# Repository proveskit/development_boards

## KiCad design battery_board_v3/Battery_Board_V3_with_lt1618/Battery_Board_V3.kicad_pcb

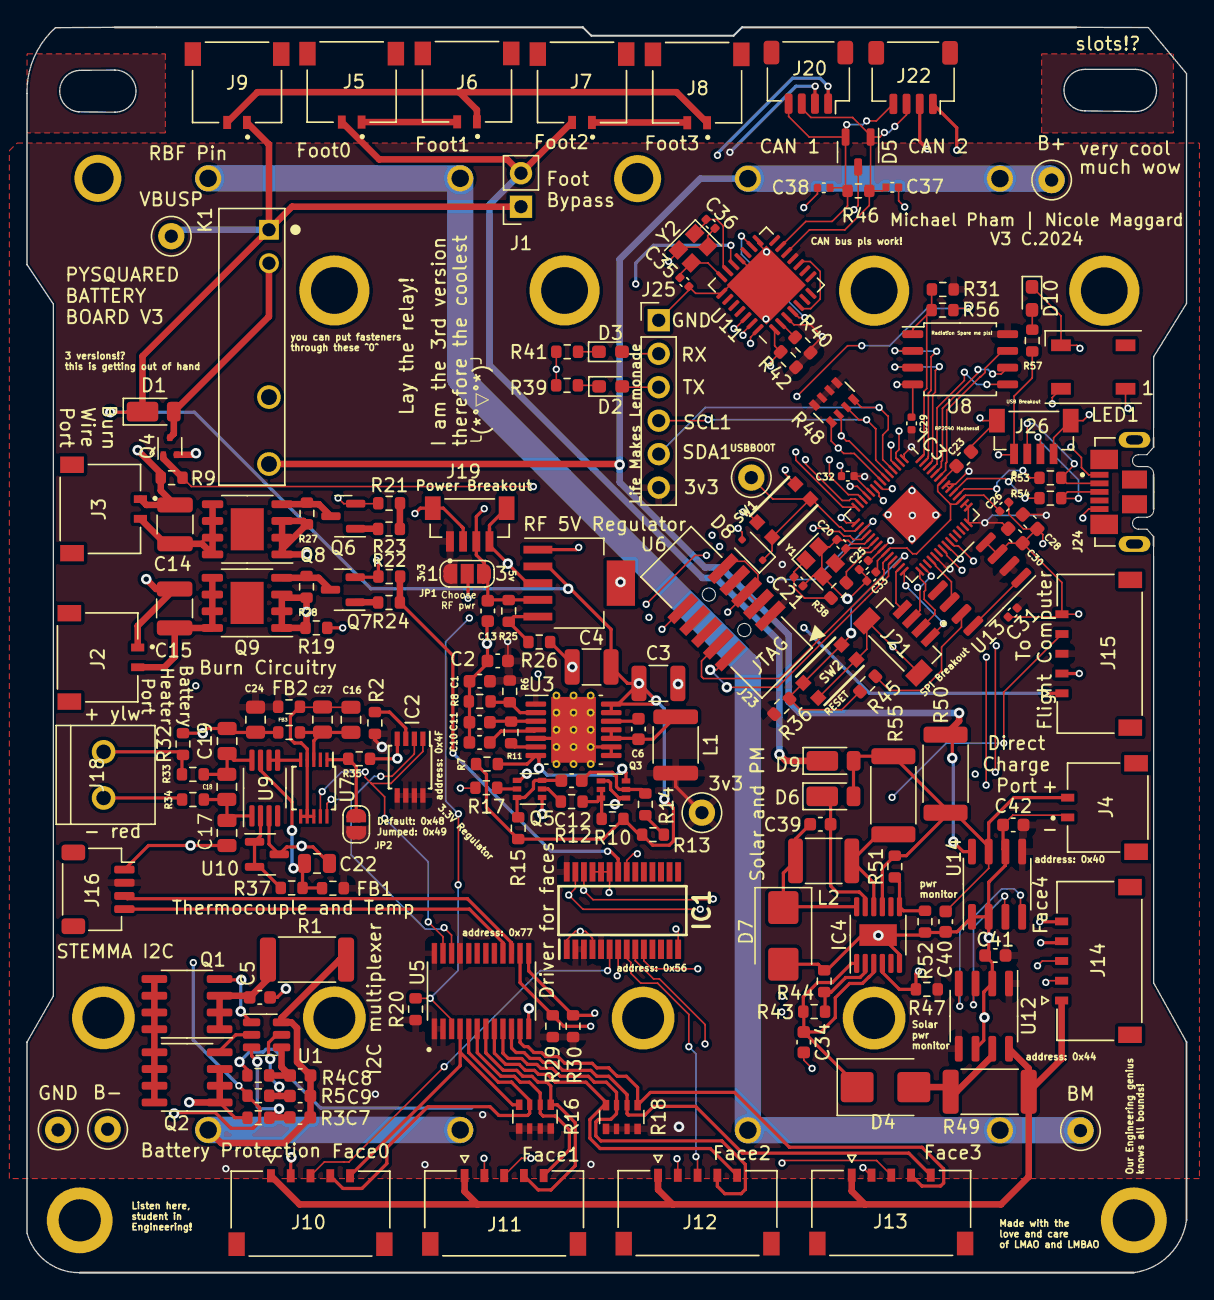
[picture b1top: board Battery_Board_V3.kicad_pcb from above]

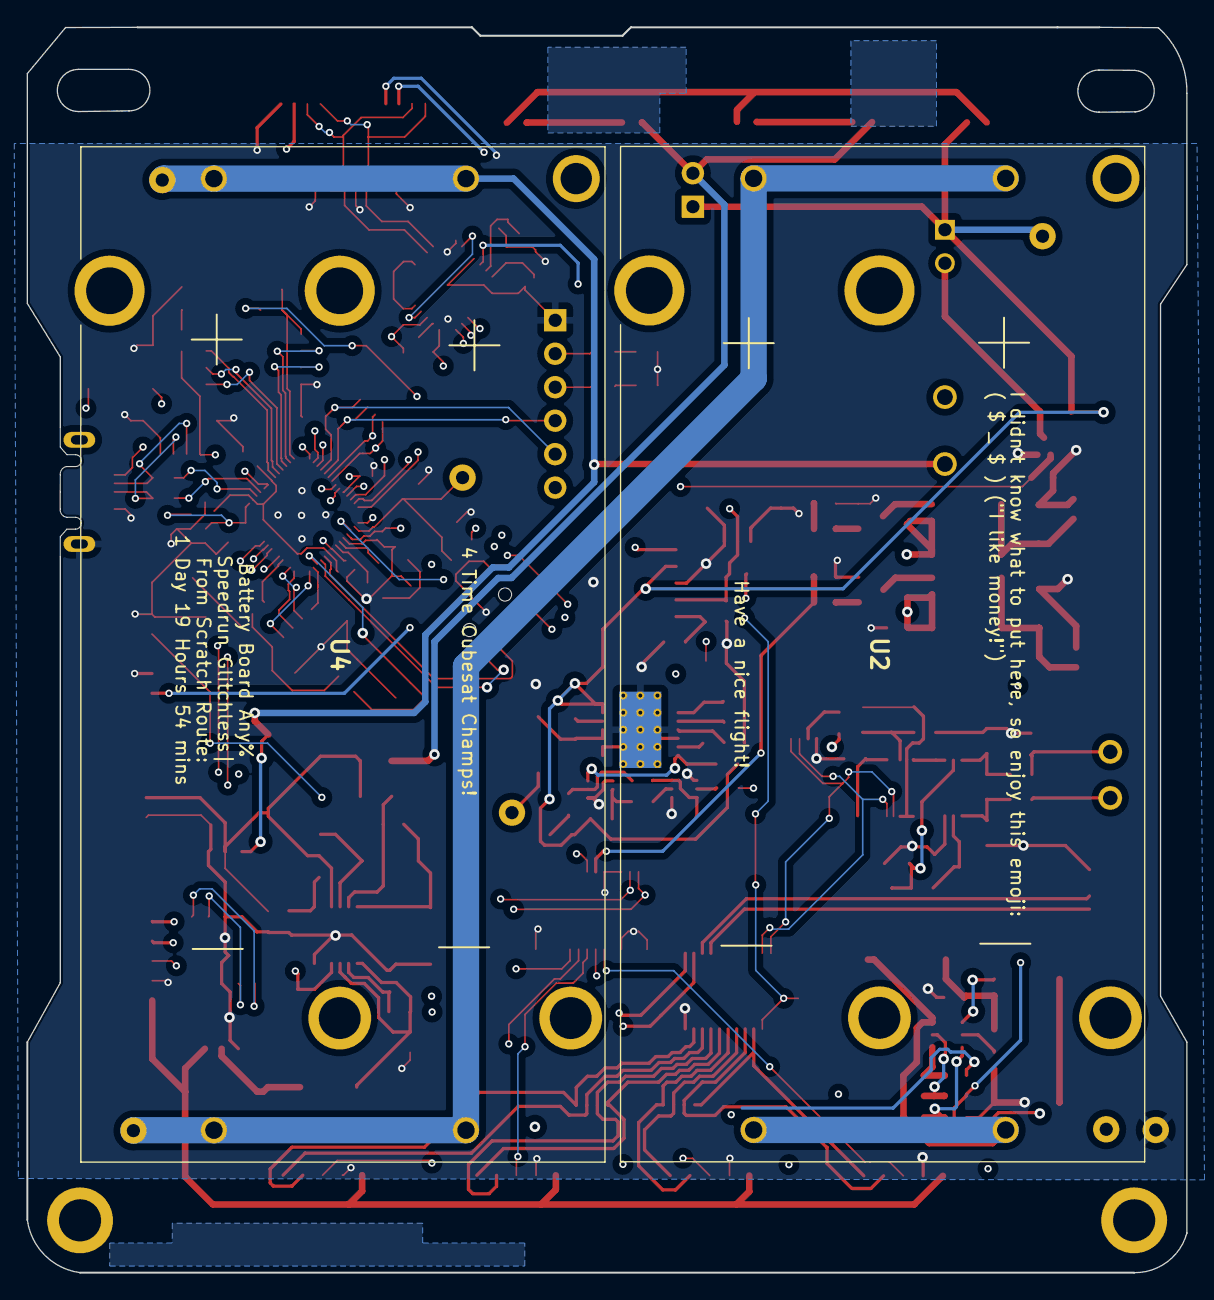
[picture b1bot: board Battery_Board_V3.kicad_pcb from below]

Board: 4 copper layers, 88.0 x 94.5 mm, 181 parts (2 on the bottom side), 135 nets.

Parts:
C1, C2: 22uF; C_0603_1608Metric
C3, C4: 100uF; C_1210_3225Metric
C5, C6, C7, C8, C9, C41, C42: 0.1uF; C_0603_1608Metric
C10: 3.3nF; C_0603_1608Metric
C11, C23, C28, C30, C39: 1uF; C_0603_1608Metric
C12, C13, C34, C40: 10uF; C_0603_1608Metric
C14, C15: 200uF; C_1210_3225Metric
C16, C24: 10uF; C_0805_2012Metric
C17, C19: 0.01uF; C_0805_2012Metric
C18, C27: 0.1uF; C_0805_2012Metric
C20, C21: 22pF; C_0402_1005Metric
C22: 1uF; C_0805_2012Metric
C25, C26, C29, C31, C32, C33: 0.1uF; C_0402_1005Metric
C35, C36: 22pf; C_0402_1005Metric
C37, C38: 47pf; C_0402_1005Metric
D1, D6, D9: DFLS130L; D_PowerDI-123
D2: green; D_0603_1608Metric_Pad1.05x0.95mm_HandSolder
D3: red; D_0603_1608Metric_Pad1.05x0.95mm_HandSolder
D4, D7: D_Schottky; D_SMB
D5: PESD1CAN; SOT-23-3
D8: NSR0320; D_SOD-323F
D10: Blue; D_0603_1608Metric_Pad1.05x0.95mm_HandSolder
FB1, FB2, FB3: FerriteBead; R_0603_1608Metric
IC1: PCA9685PW,118; SOP65P640X110-28N
IC2: PCT2075DP,118; TSSOP-8_3x3mm_P0.65mm
IC3: RP2040_QFN56; QFN-56-1EP_7x7mm_P0.4mm_EP3.2x3.2mm
IC4: LT3652IMSE#PBF; MSOP-12-1EP_3x4mm_P0.65mm_EP1.65x2.85mm
J1: Bypass; PinSocket_1x02_P2.54mm_Vertical
J2: Heater; MOLEX_504050-0291
J3: BURN; MOLEX_504050-0291
J4: CHARGE; MOLEX_504050-0291
J5: Foot0; MOLEX_504050-0291
J6: Foot1; MOLEX_504050-0291
J7: Foot2; MOLEX_504050-0291
J8: Foot3; MOLEX_504050-0291
J9: RBF; MOLEX_504050-0291
J10: Face0; MOLEX_5040500591
J11: Face1; MOLEX_5040500591
J12: Face2; MOLEX_5040500591
J13: Face3; MOLEX_5040500591
J14: Face4; MOLEX_5040500591
J15: FC; MOLEX_5040500591
J16: Breakout; JST_SH_SM04B-SRSS-TB_1x04-1MP_P1.00mm_Horizontal
J18: Screw_Terminal_01x02; ScrewTerminal
J19, J21, J26: BM04B-SRSS-TB(LF)(SN); JST_BM04B-SRSS-TB(LF)(SN)
J20: CAN1; JST_SH_SM04B-SRSS-TB_1x04-1MP_P1.00mm_Horizontal
J22: CAN2; JST_SH_SM04B-SRSS-TB_1x04-1MP_P1.00mm_Horizontal
J23: Conn_ARM_JTAG_SWD_10; JTAG_2X05_1.27MM_BOX_NOCREAM
J24: USB_B_Micro; MOLEX_105164-0001
J25: Life Makes Lemonade; PinHeader_1x06_P2.54mm_Vertical
JP1: SolderJumper_3_Open; SolderJumper-3_P1.3mm_Open_RoundedPad1.0x1.5mm_NumberLabels
JP2: SolderJumper_2_Open; SolderJumper-2_P1.3mm_Open_RoundedPad1.0x1.5mm
K1: APAN3105; RELAY_APAN3105
L1: 3.3uH; L_1812_4532Metric
L2: 10uH; L_1812_4532Metric
LED1: WS2812B_SK6812_1515; LED_WS2812B_PLCC4_5.0x5.0mm_P3.2mm
Q1, Q2: IRF7458; SOIC-8_3.9x4.9mm_P1.27mm
Q3, Q5: MBT2222ADW1T1; SOT-363_SC-70-6
Q4: MMBT2222AT; SOT-523
Q6, Q7: IRLML2803; SOT-23
Q8, Q9: NDS8434; SOIC-8-1EP_3.9x4.9mm_P1.27mm_EP2.514x3.2mm
R1: 0.01; R_2512_6332Metric
R2, R17, R20, R25, R29, R30, R47: 10K; R_0603_1608Metric
R3: 1K; R_0603_1608Metric
R4, R5: 330; R_0603_1608Metric
R6, R7: 73.2K; R_0603_1608Metric
R8: 22.1K; R_0603_1608Metric
R9, R21, R22, R31, R36, R40, R42, R45, R57: 10k; R_0603_1608Metric
R10, R11, R13, R14, R15: 100K; R_0603_1608Metric
R12: 20K; R_0603_1608Metric
R16, R18, R48: 10k; R_Array_Convex_4x0603
R19, R51: 634k; R_0603_1608Metric
R23, R24: 4.7k; R_0603_1608Metric
R26: 3.3K; R_0603_1608Metric
R27, R28: 100k; R_0603_1608Metric
R32: 1-MOhm; R_0603_1608Metric
R33, R34: 100-Ohm; R_0603_1608Metric
R35: 10k-Ohm; R_0603_1608Metric
R37, R38, R39, R41, R56: 1k; R_0603_1608Metric
R43: 200k; R_0603_1608Metric
R44: 85k; R_0603_1608Metric
R46: 120; R_0603_1608Metric
R49, R50: 0.002; R_2512_6332Metric
R52: 412k; R_0603_1608Metric
R53, R54: 22; R_0603_1608Metric
R55: 0.1; R_2512_6332Metric
SW1, SW2: KMR2; BTN_KMR2_4.6X2.8
TP1: 3v3; TestPoint_Loop_D1.80mm_Drill1.0mm_Beaded
TP2: B-; TestPoint_Loop_D1.80mm_Drill1.0mm_Beaded
TP3: BM; TestPoint_Loop_D1.80mm_Drill1.0mm_Beaded
TP4: GND; TestPoint_Loop_D1.80mm_Drill1.0mm_Beaded
TP5: B+; TestPoint_Loop_D1.80mm_Drill1.0mm_Beaded
TP6: VBUSP; TestPoint_Loop_D1.80mm_Drill1.0mm_Beaded
TP8: USBBOOT; TestPoint_Loop_D1.80mm_Drill1.0mm_Beaded
U1: R5460N208AA; SOT-23-6
U2, U4: 1049
U3: TPS54226PWPRPWP14_2P31X2P46-L; HTSSOP-14-1EP_4.4x5mm_P0.65mm_EP3.4x5mm_Mask3x3.1mm_Thermal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
U5: TCA9548APWR; SOP65P640X120-24N
U6: TPS7A4501DCQT; SOT-223-6
U7: ADS1015IDGS; TSSOP-10_3x3mm_P0.5mm
U8: W25Q128JV; SOIC-8_5.275x5.275mm_P1.27mm
U9: AD8495; MSOP-8_3x3mm_P0.65mm
U10: TLVH431 DBZ SOT-23; SOT-23
U11: MCP25625-E/ML; QFN-28-1EP_6x6mm_P0.65mm_EP4.25x4.25mm
U12, U14: INA219AxD; SOIC-8_3.9x4.9mm_P1.27mm
U13: MAX706RESA; SO-8_3.9x4.9mm_P1.27mm
Y1, Y2: Crystal_GND24; Crystal_SMD_2520-4Pin_2.5x2.0mm

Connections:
1.2V: C23.1, C25.2, C26.2, IC3.23 (DVDD), IC3.45 (VREG_VOUT), IC3.50 (DVDD)
+3V3: C1.2, C2.2, C24.2, C28.1, C29.1, C30.1, C31.1, C32.1, C33.1, C41.2, C42.2, FB1.2, FB2.2, IC1.2 (A1), IC1.3 (A2), IC1.5 (A4), IC1.28 (VDD), IC2.5 (A2), IC2.6 (A1), IC2.7 (A0), IC2.8 (VCC), IC3.1 (IOVDD), IC3.10 (IOVDD), IC3.22 (IOVDD), IC3.33 (IOVDD), IC3.42 (IOVDD), IC3.43 (ADC_IOVDD), IC3.44 (VREG_IOVDD), IC3.48 (USB_IOVDD), IC3.49 (IOVDD), J15.3, J16.2, J19.1, J20.2, J22.2, J23.1 (VTref), J25.6, JP1.1 (A), JP2.2 (B), L1.2, R2.1, R6.2, R16.5 (R4.2), R16.6 (R3.2), R16.7 (R2.2), R16.8 (R1.2), R18.5 (R4.2), R18.6 (R3.2), R18.7 (R2.2), R18.8 (R1.2), R20.1, R29.1, R30.1, R31.1, R36.1, R40.1, R42.1, R47.1, R48.5 (R4.2), R48.6 (R3.2), R48.7 (R2.2), R48.8 (R1.2), TP1.1, U3.1 (VO), U5.1 (A0), U5.2 (A1), U5.21 (A2), U5.24 (VCC), U8.8 (VCC), U11.3 (VDD@1), U11.11 (VIO), U12.1 (A1), U12.5 (VS), U13.2 (VCC), U14.5 (VS)
+5V: C13.2, J19.3, JP1.3 (B), R25.1, U6.4 (OUT), U11.19 (VDDA)
/3V3_EN: Q3.6 (C1), R7.2, U3.7 (EN)
/QSPI_CS: IC3.56 (~QSPI_CS), R31.2, R56.1, U8.1 (SSEL)
/QSPI_DATA[0]: IC3.53 (QSPI_SD0), U8.5 (MOSI)
/QSPI_DATA[1]: IC3.55 (QSPI_SD1), U8.2 (MISO)
/QSPI_DATA[2]: IC3.54 (QSPI_SD2), U8.3 (WP#/IO2)
/QSPI_DATA[3]: IC3.51 (QSPI_SD3), U8.7 (HOLD#/IO3)
/QSPI_SCK: IC3.52 (QSPI_SCLK), U8.6 (SCK)
/USBBOOT: D8.C, IC3.16 (GPIO13), SW1.A, SW1.A' (P1), TP8.1
/VDD: C9.2, R5.2, U1.5 (VDD)
/V_RF: J15.1, JP1.2 (C)
/~RESET: IC3.26 (/RUN), J23.10 (~RESET), R36.2, R45.1, SW2.A, SW2.A' (P1)
AGND: C16.2, C27.2, FB3.1, U7.3 (GND)
AVDD: C16.1, C27.1, FB2.1, U7.4 (AIN0), U7.6 (AIN2), U7.7 (AIN3), U7.8 (VDD)
B-: C7.1, C8.1, C9.1, R1.1, TP2.1, U1.6 (VSS), U2.6, U2.7
BM: R4.1, TP3.1, U2.8, U2.9, U4.6, U4.7
BURN: C14.1, J3.2, Q8.5 (Drain), Q8.6 (Drain), Q8.7 (Drain), Q8.8 (Drain)
BURN_RELAY_A: IC3.18 (GPIO15), Q4.1 (B), R9.1
Break_SCL: J16.4, U5.16 (SC5)
Break_SDA: J16.3, U5.15 (SD5)
CANH: C38.2, D5.2, J20.4, J22.4, R46.2, U11.13 (CANH)
CANL: C37.1, D5.1, J20.3, J22.3, R46.1, U11.12 (CANL)
CHRG': IC3.35 (GPIO23), IC4.4 (~CHRG), R47.2
D+: J24.3 (D+), J26.3, R54.2
D-: J24.2 (D-), J26.2, R53.2
ENAB_BURN: R21.1, R23.2
ENAB_HEATER: IC1.22 (LED15), R22.1, R24.2
ENAB_RF: IC3.15 (GPIO12), U6.1 (~SHDN)
F0_ENB: IC1.6 (LED0), J10.3
F0_SCL: J10.4, R16.3 (R3.1), U5.5 (SC0)
F0_SDA: J10.5, R16.4 (R4.1), U5.4 (SD0)
F1_ENB: IC1.7 (LED1), J11.3
F1_SCL: J11.4, R16.1 (R1.1), U5.7 (SC1)
F1_SDA: J11.5, R16.2 (R2.1), U5.6 (SD1)
F2_ENB: IC1.8 (LED2), J12.3
F2_SCL: J12.4, R18.3 (R3.1), U5.9 (SC2)
F2_SDA: J12.5, R18.4 (R4.1), U5.8 (SD2)
F3_ENB: IC1.9 (LED3), J13.3
F3_SCL: J13.4, R18.1 (R1.1), U5.11 (SC3)
F3_SDA: J13.5, R18.2 (R2.1), U5.10 (SD3)
F4_ENB: IC1.10 (LED4), J14.3
F4_SCL: J14.4, R29.2, U5.14 (SC4)
F4_SDA: J14.5, R30.2, U5.13 (SD4)
FC_RESET: IC1.21 (LED14), J15.4
FC_RX: D3.A, IC3.2 (GPIO0), J25.2
FC_TX: D2.A, IC3.3 (GPIO1), J25.3
GND: C1.1, C2.1, C3.2, C4.2, C5.2, C10.2, C11.2, C13.1, C14.2, C15.2, C17.1, C19.2, C20.1, C21.1, C22.2, C23.2, C24.1, C25.1, C26.1, C28.2, C29.2, C30.2, C31.2, C32.2, C33.2, C34.2, C35.2, C36.2, C37.2, C38.1, C40.2, C41.1, C42.1, D5.3, D7.2 (A), D10.C, FB3.2, IC1.1 (A0), IC1.4 (A3), IC1.14 (VSS), IC1.23 (~OE), IC1.24 (A5), IC1.25 (EXTCLK), IC2.4 (GND), IC3.19 (TESTEN), IC3.57 (GND), IC4.6 (TIMER), IC4.13 (EP), J2.1, J3.1, J4.1, J10.2, J11.2, J12.2, J13.2, J14.2, J15.2, J15.5, J16.1, J19.2, J19.4, J19.S1 (SHIELD), J19.S2 (SHIELD), J20.1, J21.S1 (SHIELD), J21.S2 (SHIELD), J22.1, J23.3 (GND), J23.5 (GND), J23.9 (GNDDetect), J24.5 (GND), J24.SH1 (Shield), J25.1, J26.4, J26.S1 (SHIELD), J26.S2 (SHIELD), LED1.3 (GND), Q2.1 (S), Q2.2 (S), Q2.3 (S), Q3.1 (E1), Q3.4 (E2), Q4.2 (E), Q5.1 (E1), Q5.4 (E2), Q6.2 (S), Q7.2 (S), R3.2, R8.1, R9.2, R19.1, R21.2, R22.2, R26.2, R32.2, R35.1, R39.2, R41.2, R44.1, R52.1, SW1.B (S), SW1.B' (S1), SW2.B (S), SW2.B' (S1), TP4.1, U3.5 (GND), U3.8 (PGND1), U3.9 (PGND2), U3.15 (EPAD), U5.12 (GND), U6.3 (GND_1), U6.6 (GND_2), U8.4 (VSS), U9.3 (-Vs), U10.3 (A), U11.15 (STBY), U11.18 (VSS@1), U11.22 (GND), U11.29 (GND@1), U12.2 (A0), U12.6 (GND), U13.3 (GND), U13.4 (PFI), U14.1 (A1), U14.2 (A0), U14.6 (GND), Y1.2, Y1.4, Y2.2, Y2.4
Heater: C15.1, J2.2, Q9.5 (Drain), Q9.6 (Drain), Q9.7 (Drain), Q9.8 (Drain)
I2C_RESET: IC3.9 (GPIO7), R20.2, U5.3 (~RESET)
NEOPIX: IC3.36 (GPIO24), LED1.4 (DI)
NEO_PWR: IC3.37 (GPIO25), LED1.1 (VDD)
unnamed: C5.1, Q1.1 (S), Q1.2 (S), Q1.3 (S), R1.2
unnamed: C21.2, R38.2, Y1.1
unnamed: D2.C, R39.1
unnamed: D3.C, R41.1
unnamed: C34.1, D4.1 (K), IC4.1 (VIN), IC4.3 (~SHDN), R43.1
unnamed: C39.1, D7.1 (K), IC4.12 (SW), L2.1
unnamed: D8.A, R56.2
unnamed: D10.A, R57.2
unnamed: IC2.3 (OS), R2.2
unnamed: C20.2, IC3.20 (XIN), Y1.3
unnamed: IC3.21 (XOUT), R38.1
unnamed: C39.2, D6.C, IC4.11 (BOOST)
unnamed: IC4.10 (SENSE), L2.2, R55.2
unnamed: IC4.7 (VFB), R51.1, R52.2
unnamed: IC4.2 (VIN_REG), R43.2, R44.2
unnamed: J5.1, J6.2
unnamed: J7.1, J8.2
unnamed: J18.1, R33.1
unnamed: J18.2, R32.1, R34.2
unnamed: JP2.1 (A), R35.2, U7.1 (ADDR)
unnamed: K1.NO, Q8.1 (Source), Q8.2 (Source), Q8.3 (Source), Q9.1 (Source), Q9.2 (Source), Q9.3 (Source), R19.2, R27.2, R28.2
unnamed: Q1.5 (D), Q1.6 (D), Q1.7 (D), Q1.8 (D), Q2.5 (D), Q2.6 (D), Q2.7 (D), Q2.8 (D)
unnamed: Q1.4 (G), U1.1 (DOUT)
unnamed: Q2.4 (G), U1.2 (COUT)
unnamed: Q3.2 (B1), Q3.3 (C2), R10.2, R12.2
unnamed: C12.2, Q3.5 (B2), R14.2
unnamed: D1.A, K1.C2, Q4.3 (C)
unnamed: Q5.2 (B1), R12.1
unnamed: C12.1, Q5.3 (C2), Q5.6 (C1), R15.2
unnamed: Q5.5 (B2), R17.1
unnamed: Q6.3 (D), Q8.4 (Gate), R27.1
unnamed: Q6.1 (G), R23.1
unnamed: Q7.3 (D), Q9.4 (Gate), R28.1
unnamed: Q7.1 (G), R24.1
unnamed: R13.2, R14.1
unnamed: C7.2, R3.1, U1.3 (V-)
unnamed: C8.2, R4.2, U1.4 (VC)
unnamed: R11.1, U3.6 (PG)
unnamed: C10.1, U3.4 (SS)
unnamed: C6.1, L1.1, U3.10 (SW1), U3.11 (SW2)
unnamed: C6.2, U3.12 (VBST)
unnamed: R6.1, R8.2, U3.2 (VFB)
unnamed: C11.1, R11.2, U3.3 (VREG5)
unnamed: R25.2, R26.1, U6.5 (SENSE/ADJ)
unnamed: C18.1, C19.1, R34.1, U9.8 (+IN)
unnamed: C22.1, FB1.1, R37.2, U9.7 (+Vs)
unnamed: C17.2, C18.2, R33.2, U9.1 (-IN)
unnamed: R37.1, U9.2 (REF), U10.1 (K), U10.2 (REF)
unnamed: C35.1, U11.21 (OSC1), Y2.3
unnamed: C36.1, U11.20 (OSC2), Y2.1
unnamed: R40.2, U11.2 (RESET)
unnamed: U13.1 (~MR), U13.8 (~WDO)
unnamed: R45.2, U13.7 (~RESET)
OUT: U7.5 (AIN1), U9.5 (SENSE), U9.6
PACK+: K1.M, R5.1, R50.2, TP5.1, U4.8, U4.9, U14.8 (IN+)
RXCAN: U11.5 (RXCAN), U11.10 (RXD)
SCL0: IC1.26 (SCL), IC2.2 (SCL), IC3.7 (GPIO5), R48.1 (R1.1), U5.22 (SCL), U7.10 (SCL), U12.4 (SCL), U14.4 (SCL)
SCL1: IC3.5 (GPIO3), J25.4, R48.3 (R3.1)
SDA0: IC1.27 (SDA), IC2.1 (SDA), IC3.6 (GPIO4), R48.2 (R2.1), U5.23 (SDA), U7.9 (SDA), U12.3 (SDA), U14.3 (SDA)
SDA1: IC3.4 (GPIO2), J25.5, R48.4 (R4.1)
SPI0_CS0: IC3.12 (GPIO9), R42.2, U11.1 (CS)
SPI0_MISO: IC3.11 (GPIO8), U11.28 (SO)
SPI0_MOSI: IC3.14 (GPIO11), U11.27 (SI)
SPI0_SCK: IC3.13 (GPIO10), U11.26 (SCK)
SPI1_CS0: IC3.28 (GPIO17), J21.1
SPI1_MISO: IC3.27 (GPIO16), J21.4
SPI1_MOSI: IC3.30 (GPIO19), J21.3
SPI1_SCK: IC3.29 (GPIO18), J21.2
SWCLK: IC3.24 (SWCLK), J23.4 (SWDCLK/TCK)
SWDIO: IC3.25 (SWDIO), J23.2 (SWDIO/TMS)
TXCAN: U11.4 (TXCAN), U11.16 (TXD)
USB_D+: IC3.47 (USB_D+), R54.1
USB_D-: IC3.46 (USB_D-), R53.1
VBATT_SENSE: C40.1, D6.A, D9.A, IC4.9 (BAT), J4.2, R50.1, R51.2, R55.1, U14.7 (IN-)
VBUS: J24.1 (VBUS), J26.1, R57.1
VBUSP: C3.1, C4.1, D1.C, J1.1, J9.1, K1.C1, R7.1, R10.1, R13.1, R15.1, TP6.1, U3.13 (VIN), U3.14 (VCC), U6.2 (IN)
VBUS_RESET: IC3.17 (GPIO14), R17.2
VBatt: D9.C, J1.2, J5.2, J7.2
VBatt1: J6.1, J8.1, J9.2
VSOLAR: J10.1, J11.1, J12.1, J13.1, J14.1, R49.2, U12.8 (IN+)
VSOLAR_I: D4.2 (A), R49.1, U12.7 (IN-)
WDT_WDI: IC3.32 (GPIO21), U13.6 (~WDI)

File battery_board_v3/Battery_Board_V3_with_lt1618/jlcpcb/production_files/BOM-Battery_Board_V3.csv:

Comment,Designator,Footprint,LCSC
FerriteBead,"FB1,FB2,FB3",R_0603_1608Metric,C1002
73.2K,"R6,R7",R_0603_1608Metric,C101180
IRF7458,"Q1,Q2",SOIC-8_3.9x4.9mm_P1.27mm,C10879
0.002,"R49,R50",R_2512_6332Metric,C108929
10k,"R16,R18,R48",R_Array_Convex_4x0603,C111802
TCA9548APWR,U5,SOP65P640X120-24N,C130026
TPS54226PWPRPWP14_2P31X2P46-L,U3,HTSSOP-14-1EP_4.4x5mm_P0.65mm_EP3.4x5mm_Mask3x3.1mm_ThermalVias,C1355858
INA219AxD,"U12,U14",SOIC-8_3.9x4.9mm_P1.27mm,C138706
0.1uF,"C41,C42,C5,C6,C7,C8,C9",C_0603_1608Metric,C14663
DFLS130L,"D1,D6,D9",D_PowerDI-123,C150474
0.1uF,"C25,C26,C29,C31,C32,C33",C_0402_1005Metric,C1525
22pF,"C20,C21,C35,C36",C_0402_1005Metric,C1555
47pf,"C37,C38",C_0402_1005Metric,C1567
PESD1CAN,D5,SOT-23-3,C15771
1uF,"C11,C23,C28,C30,C39",C_0603_1608Metric,C15849
10uF,"C16,C24",C_0805_2012Metric,C15850
BM04B-SRSS-TB(LF)(SN),"J19,J21,J26",JST_BM04B-SRSS-TB(LF)(SN),C160390
Breakout,"J16,J20,J22",JST_SH_SM04B-SRSS-TB_1x04-1MP_P1.00mm_Horizontal,C160404
3.3nF,C10,C_0603_1608Metric,C1613
0.01uF,"C17,C19",C_0805_2012Metric,C1710
MMBT2222AT,Q4,SOT-523,C190608
"PCT2075DP,118",IC2,TSSOP-8_3x3mm_P0.65mm,C192518
ADS1015IDGS,U7,TSSOP-10_3x3mm_P0.5mm,C193969
10uF,"C12,C13,C34,C40",C_0603_1608Metric,C19702
RP2040_QFN56,IC3,QFN-56-1EP_7x7mm_P0.4mm_EP3.2x3.2mm,C2040
1K,"R3,R37,R38,R39,R41,R56",R_0603_1608Metric,C21190
TLVH431 DBZ SOT-23,U10,SOT-23,C2156576
85k,R44,R_0603_1608Metric,C227531
100-Ohm,"R33,R34",R_0603_1608Metric,C22775
120,R46,R_0603_1608Metric,C22787
red,D3,D_0603_1608Metric_Pad1.05x0.95mm_HandSolder,C2286
1-MOhm,R32,R_0603_1608Metric,C22935
3.3K,R26,R_0603_1608Metric,C22978
412k,R52,R_0603_1608Metric,C23050
330,"R4,R5",R_0603_1608Metric,C23138
4.7k,"R23,R24",R_0603_1608Metric,C23162
22,"R53,R54",R_0603_1608Metric,C23345
USB_B_Micro,J24,MOLEX_105164-0001,C234179
200uF,"C14,C15,C3,C4",C_1210_3225Metric,C23742
Crystal_GND24,Y1,Crystal_SMD_2520-4Pin_2.5x2.0mm,C252259
0.1,R55,R_2512_6332Metric,C25466
10K,"R17,R2,R20,R21,R22,R25,R29,R30,R31,R35,R36,R40,R42,R45,R47,R57,R9",R_0603_1608Metric,C25804
200k,R43,R_0603_1608Metric,C25811
22.1K,R8,R_0603_1608Metric,C25961
R5460N208AA,U1,SOT-23-6,C259714
"PCA9685PW,118",IC1,SOP65P640X110-28N,C2678753
0.1uF,"C18,C27",C_0805_2012Metric,C28233
1uF,C22,C_0805_2012Metric,C28323
MAX706RESA,U13,SO-8_3.9x4.9mm_P1.27mm,C28380
Crystal_GND24,Y2,Crystal_SMD_2520-4Pin_2.5x2.0mm,C284158
WS2812B_SK6812_1515,LED1,LED_WS2812B_PLCC4_5.0x5.0mm_P3.2mm,C2843785
D_Schottky,"D4,D7",D_SMB,C2892544
NDS8434,"Q8,Q9",SOIC-8-1EP_3.9x4.9mm_P1.27mm_EP2.514x3.2mm,C2997
Screw_Terminal_01x02,J18,ScrewTerminal,C2997509
20K,R12,R_0603_1608Metric,C4184
100K,"R10,R11,R13,R14,R15,R27,R28",R_0603_1608Metric,C427284
LT3652IMSE#PBF,IC4,MSOP-12-1EP_3x4mm_P0.65mm_EP1.65x2.85mm,C459874
MCP25625-E/ML,U11,QFN-28-1EP_6x6mm_P0.65mm_EP4.25x4.25mm,C481365
NSR0320,D8,D_SOD-323F,C48192
IRLML2803,"Q6,Q7",SOT-23,C558175
MBT2222ADW1T1,"Q3,Q5",SOT-363_SC-70-6,C559075
22uF,"C1,C2",C_0603_1608Metric,C59461
AD8495,U9,MSOP-8_3x3mm_P0.65mm,C59658
634k,"R19,R51",R_0603_1608Metric,C65831
green,D2,D_0603_1608Metric_Pad1.05x0.95mm_HandSolder,C72040
Blue,D10,D_0603_1608Metric_Pad1.05x0.95mm_HandSolder,C72041
KMR2,"SW1,SW2",BTN_KMR2_4.6X2.8,C72443
0.01,R1,R_2512_6332Metric,C76243
TPS7A4501DCQT,U6,SOT-223-6,C840094
W25Q128JV,U8,SOIC-8_5.275x5.275mm_P1.27mm,C97521
10uH,L2,L_1812_4532Metric,C99792
3.3uH,L1,L_1812_4532Metric,C99794
Foot1,J6,MOLEX_504050-0291,
Face1,J11,MOLEX_5040500591,
CHARGE,J4,MOLEX_504050-0291,
FC,J15,MOLEX_5040500591,
Face3,J13,MOLEX_5040500591,
Face2,J12,MOLEX_5040500591,
1049,U2,1049,
1049,U4,1049,
Bypass,J1,PinSocket_1x02_P2.54mm_Vertical,
SolderJumper_3_Open,JP1,SolderJumper-3_P1.3mm_Open_RoundedPad1.0x1.5mm_NumberLabels,
Heater,J2,MOLEX_504050-0291,
APAN3105,K1,RELAY_APAN3105,
BURN,J3,MOLEX_504050-0291,
Foot0,J5,MOLEX_504050-0291,
Face4,J14,MOLEX_5040500591,
VBUSP,TP6,TestPoint_Loop_D1.80mm_Drill1.0mm_Beaded,
B+,TP5,TestPoint_Loop_D1.80mm_Drill1.0mm_Beaded,
GND,TP4,TestPoint_Loop_D1.80mm_Drill1.0mm_Beaded,
BM,TP3,TestPoint_Loop_D1.80mm_Drill1.0mm_Beaded,
B-,TP2,TestPoint_Loop_D1.80mm_Drill1.0mm_Beaded,
3v3,TP1,TestPoint_Loop_D1.80mm_Drill1.0mm_Beaded,
Foot2,J7,MOLEX_504050-0291,
Foot3,J8,MOLEX_504050-0291,
Life Makes Lemonade,J25,PinHeader_1x06_P2.54mm_Vertical,
USBBOOT,TP8,TestPoint_Loop_D1.80mm_Drill1.0mm_Beaded,
Face0,J10,MOLEX_5040500591,
Conn_ARM_JTAG_SWD_10,J23,JTAG_2X05_1.27MM_BOX_NOCREAM,
RBF,J9,MOLEX_504050-0291,
SolderJumper_2_Open,JP2,SolderJumper-2_P1.3mm_Open_RoundedPad1.0x1.5mm,

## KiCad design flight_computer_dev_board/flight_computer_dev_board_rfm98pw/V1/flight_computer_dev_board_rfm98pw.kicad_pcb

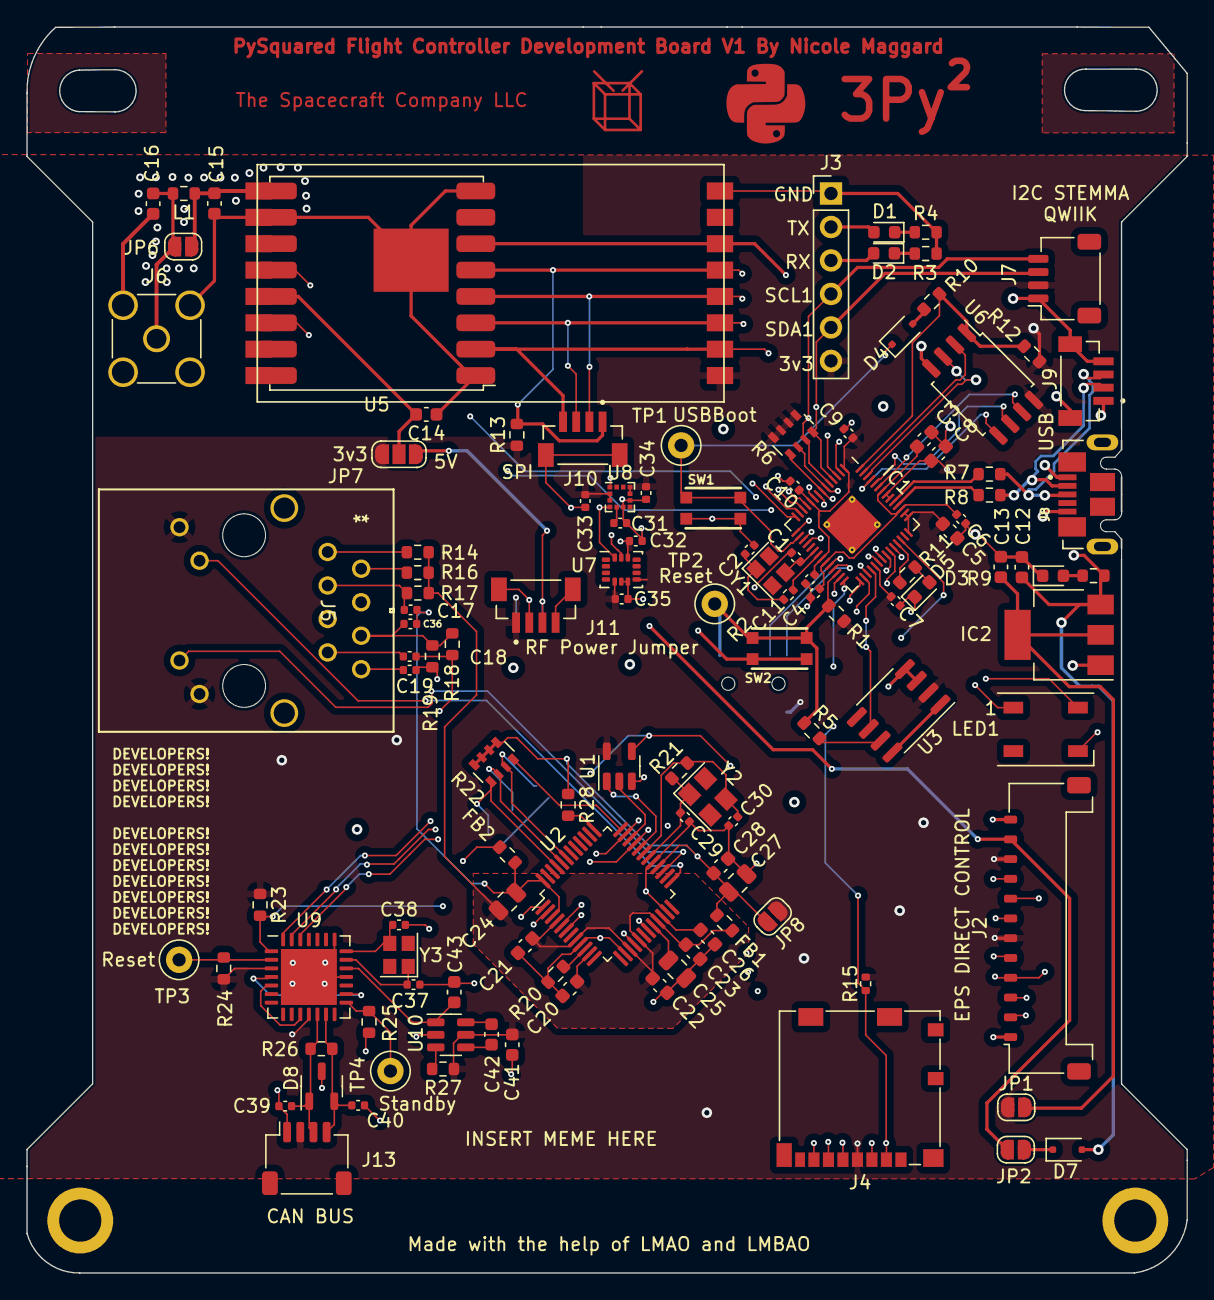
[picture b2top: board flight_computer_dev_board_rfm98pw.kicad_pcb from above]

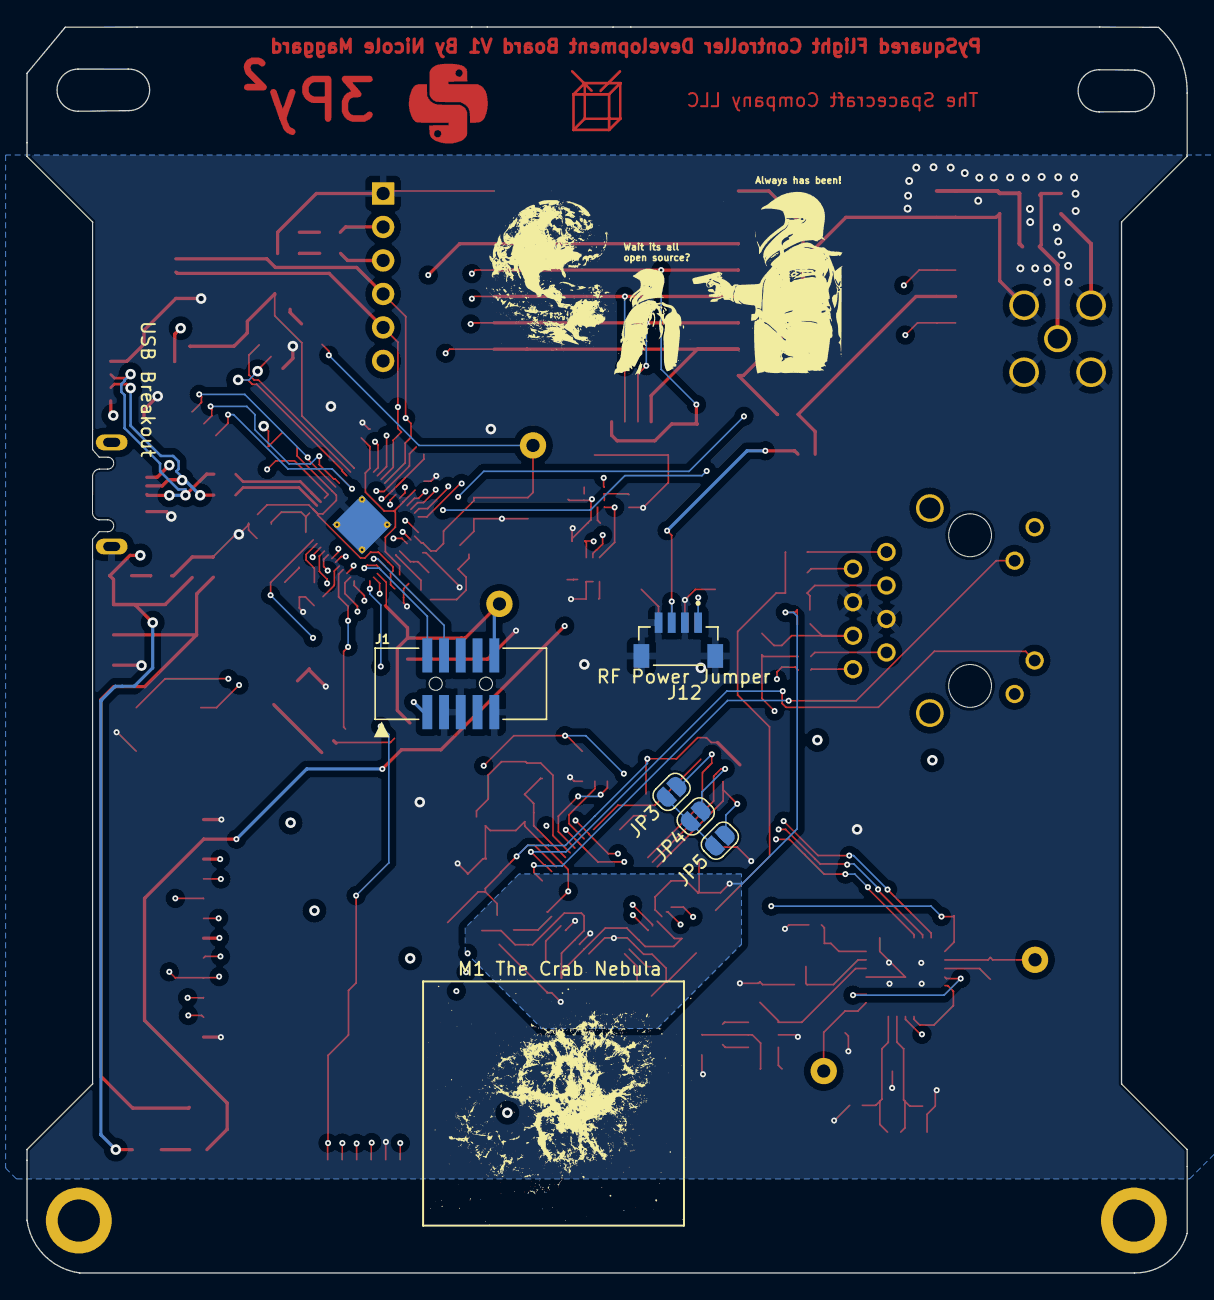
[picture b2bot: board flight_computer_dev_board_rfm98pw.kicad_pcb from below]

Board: 4 copper layers, 88.0 x 94.5 mm, 124 parts (5 on the bottom side), 100 nets.

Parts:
C1, C2, C29, C30: 22pF; C_0402_1005Metric
C3, C6, C8: 1uF; C_0603_1608Metric
C4, C5, C7, C9, C10, C11, C32, C33, C34, C35: 100nf; C_0402_1005Metric
C12, C14: 10uF; C_0603_1608Metric
C13: 22uF; C_0603_1608Metric
C15, C16: DNI; C_0603_1608Metric
C17, C36: 10nf; C_0402_1005Metric
C18, C19: 6.8nf; C_0402_1005Metric
C20, C21, C22, C23, C26, C28: 0.1uF; C_0603_1608Metric
C24, C25, C27: 10uF; C_0805_2012Metric
C31: 220nf; C_0402_1005Metric
C37, C38: 22pf; C_0402_1005Metric
C39, C40: 47pf; C_0402_1005Metric
C41, C43: 10uf; C_0603_1608Metric
C42: 1uf; C_0603_1608Metric
D1, D2, D3, D5: LED; LED_0603_1608Metric
D4, D7: NSR0320; D_SOD-323F
D8: PESD1CAN; SOT-23-3
FB1, FB2: FerriteBead; R_0603_1608Metric
IC1: RP2040_QFN56; QFN-56-1EP_7x7mm_P0.4mm_EP3.2x3.2mm_ThermalVias
IC2: AZ1117CH-3.3TRG1; SOT-223
J1: Conn_ARM_JTAG_SWD_10; JTAG_2X05_1.27MM_BOX_NOCREAM
J2: FC to EPS Connector; Molex_Pico-Lock_504050-1291_1x12-1MP_P1.50mm_Horizontal
J3: Life Makes Lemonade; PinHeader_1x06_P2.54mm_Vertical
J4: 104031-0811; microSD_HC_Molex_104031-0811
J5: RJ45_LED_Shielded; RB1-125BAG1A_WIZ
J6: Conn_Coaxial; SMA_Amphenol_901-144_Vertical
J7, J13: Breakout; JST_SH_SM04B-SRSS-TB_1x04-1MP_P1.00mm_Horizontal
J8: USB_B_Micro; MOLEX_105164-0001
J9, J10, J11, J12: BM04B-SRSS-TB(LF)(SN); JST_BM04B-SRSS-TB(LF)(SN)
JP1, JP2, JP3, JP4, JP5, JP6, JP8: SolderJumper_2_Open; SolderJumper-2_P1.3mm_Open_RoundedPad1.0x1.5mm
JP7: SolderJumper_3_Open; SolderJumper-3_P1.3mm_Open_RoundedPad1.0x1.5mm_NumberLabels
L1: DNI; R_0603_1608Metric
LED1: WS2812B_SK6812_1515; LED_WS2812B_PLCC4_5.0x5.0mm_P3.2mm
R1, R5, R9, R11, R12, R13, R23, R24, R25, R27, R28: 10k; R_0603_1608Metric
R2: 1k; R_0402_1005Metric
R3, R4, R10: 1k; R_0603_1608Metric
R6, R22: 10k; R_Array_Convex_4x0603
R7, R8: 22; R_0603_1608Metric
R14, R16, R18, R19: 49.9; R_0603_1608Metric
R15: 10k; R_0402_1005Metric
R17: 10; R_0603_1608Metric
R20: 12.4k; R_0603_1608Metric
R21: 1M; R_0603_1608Metric
R26: 120; R_0603_1608Metric
SW1, SW2: KMR2; BTN_KMR2_4.6X2.8
TP1: USBBOOT; TestPoint_Loop_D1.80mm_Drill1.0mm_Beaded
TP2, TP3: RESET; TestPoint_Loop_D1.80mm_Drill1.0mm_Beaded
TP4: Standby; TestPoint_Loop_D1.80mm_Drill1.0mm_Beaded
U1: SN74AHC1G125DBVR; SOT-23-5
U2: W5500; LQFP-48_7x7mm_P0.5mm
U3: MAX706RESA; SO-8_3.9x4.9mm_P1.27mm
U4: RFM98PW
U5: RFM9xBreakout; HOPERF_RFM9XW_SMD
U6: W25Q128JV; SOIC-8_5.275x5.275mm_P1.27mm
U7: LSM6DSOTR; LGA-14_3x2.5mm_P0.5mm_LayoutBorder3x4y
U8: LSM303AGRTR; LGA-12_2x2mm_P0.5mm
U9: MCP25625-E/ML; QFN-28-1EP_6x6mm_P0.65mm_EP4.25x4.25mm
U10: AP3602AKTR-G1; SOT-23-6
Y1: 12MHZ; Crystal_SMD_2520-4Pin_2.5x2.0mm
Y2: 25MHz; Crystal_SMD_3225-4Pin_3.2x2.5mm
Y3: 16MHZ 12 pf; Crystal_SMD_2520-4Pin_2.5x2.0mm

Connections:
1.2V: C3.1, C4.2, C5.2, IC1.23 (DVDD), IC1.45 (VREG_VOUT), IC1.50 (DVDD)
3.3V: C6.1, C7.1, C8.1, C9.1, C10.1, C11.1, C32.1, C33.1, C34.1, C35.1, C41.2, IC1.1 (IOVDD), IC1.10 (IOVDD), IC1.22 (IOVDD), IC1.33 (IOVDD), IC1.42 (IOVDD), IC1.43 (ADC_IOVDD), IC1.44 (VREG_IOVDD), IC1.48 (USB_IOVDD), IC1.49 (IOVDD), J1.1 (VTref), J2.6, J2.10, J3.6, J4.4 (VDD), J5.10, J5.12, J7.2, J11.1, J12.1, J13.2, JP1.1 (A), JP7.3 (B), JP8.1 (A), R1.1, R6.5 (R4.2), R6.6 (R3.2), R6.7 (R2.2), R6.8 (R1.2), R12.1, R13.1, R15.2, R23.1, R24.1, R27.1, U1.5 (VCC), U3.2 (VCC), U4.9 (3.3V), U6.8 (VCC), U7.5 (VDDIO), U7.8 (VDD), U7.12 (CS), U8.2 (CS_XL), U8.3 (CS_MAG), U8.9 (VDD), U8.10 (VDD_IO), U9.3 (VDD@1), U9.11 (VIO), U10.5 (VIN)
3v3 Spec: C13.1, IC2.2 (OUTPUT), IC2.4 (VOUT), JP1.2 (B)
3v3_prime: C27.1, C28.1, FB1.1, JP8.2 (B), R22.5 (R4.2), R22.6 (R3.2), R22.7 (R2.2), R22.8 (R1.2), R28.1, U2.28 (VDD)
+5V: C43.2, U9.19 (VDDA), U10.1 (VOUT)
/D+: IC1.47 (USB_D+), R7.1
/D-: IC1.46 (USB_D-), R8.1
/QSPI_CS: IC1.56 (~QSPI_CS), R10.1, R12.2, U6.1 (SSEL)
/QSPI_DATA[0]: IC1.53 (QSPI_SD0), U6.5 (MOSI)
/QSPI_DATA[1]: IC1.55 (QSPI_SD1), U6.2 (MISO)
/QSPI_DATA[2]: IC1.54 (QSPI_SD2), U6.3 (WP#/IO2)
/QSPI_DATA[3]: IC1.51 (QSPI_SD3), U6.7 (HOLD#/IO3)
/QSPI_SCK: IC1.52 (QSPI_SCLK), U6.6 (SCK)
/USBBOOT: D4.1 (K), IC1.16 (GPIO13), SW1.A, SW1.A' (P1), TP1.1
/~RESET: IC1.26 (/RUN), J1.10 (~RESET), R1.2, R5.1, SW2.A, SW2.A' (P1), TP2.1
BURN_RELAY_A: IC1.18 (GPIO15), J2.2
CANH: C40.2, D8.2, J13.4, R26.2, U9.13 (CANH)
CANL: C39.1, D8.1, J13.3, R26.1, U9.12 (CANL)
ENABLE_BURN: IC1.8 (GPIO6), J2.9
ENAB_RF: IC1.15 (GPIO12), J2.5
GND: C1.1, C2.1, C3.2, C4.1, C5.1, C6.2, C7.2, C8.2, C9.2, C10.2, C11.2, C12.2, C13.2, C14.1, C15.2, C16.2, C27.2, C28.2, C29.2, C30.2, C31.2, C32.2, C33.2, C34.2, C35.2, C37.2, C38.2, C39.2, C40.1, C41.1, C43.1, D3.1 (K), D5.1 (K), D8.3, FB2.1, IC1.57 (GND), IC2.1 (ADJ/GND), J1.3 (GND), J1.5 (GND), J1.9 (GNDDetect), J2.1, J2.12, J3.1, J4.6 (VSS), J5.4, J5.5, J6.2 (Ext), J7.1, J8.5 (GND), J8.SH1 (Shield), J9.4, J9.S1 (SHIELD), J9.S2 (SHIELD), J10.S1 (SHIELD), J10.S2 (SHIELD), J11.2, J11.4, J11.S1 (SHIELD), J11.S2 (SHIELD), J12.2, J12.4, J12.S1 (SHIELD), J12.S2 (SHIELD), J13.1, LED1.3 (GND), R3.2, R4.2, R25.1, SW1.B (S), SW1.B' (S1), SW2.B (S), SW2.B' (S1), U1.3 (GND), U2.23 (RSVD), U2.29 (GND), U3.3 (GND), U3.4 (PFI), U4.2 (GND), U4.16 (GND), U4.17 (GND), U5.1 (GND), U5.8 (GND), U5.10 (GND), U6.4 (VSS), U7.6 (GND), U7.7 (GND), U8.6 (GND), U8.8 (GND), U9.18 (VSS@1), U9.22 (GND), U9.29 (GND@1), U10.2 (GND)
GNDA: C17.2, C20.2, C21.2, C22.2, C23.2, C24.2, C25.1, C26.1, C36.2, FB2.2, R20.1, U2.3 (AGND), U2.9 (AGND), U2.14 (AGND), U2.16 (AGND), U2.19 (AGND), U2.48 (AGND)
GREENLED: J5.11, U2.25 (LINKLED)
I2C_RESET: IC1.9 (GPIO7), J2.4
MISO_ETHER: U1.2 (A), U2.34 (MISO)
NEOPIX: IC1.36 (GPIO24), LED1.4 (DI)
NEO_PWR: IC1.37 (GPIO25), LED1.1 (VDD)
unnamed: C2.2, R2.2, Y1.1
unnamed: C18.1, J5.7
unnamed: C19.1, J5.8
unnamed: D1.1 (K), R4.1
unnamed: D2.1 (K), R3.1
unnamed: D3.2 (A), R9.2
unnamed: D4.2 (A), R10.2
unnamed: D5.2 (A), R11.2
unnamed: D7.1 (K), JP2.2 (B)
unnamed: C1.2, IC1.20 (XIN), Y1.3 (2)
unnamed: IC1.21 (XOUT), R2.1
unnamed: C16.1, J6.1 (In), JP6.1 (A), L1.2
unnamed: JP3.1 (A), JP4.1 (A), JP5.1 (A)
unnamed: JP3.2 (B), R22.3 (R3.1), U2.43 (PMODE2)
unnamed: JP4.2 (B), R22.2 (R2.1), U2.44 (PMODE1)
unnamed: JP5.2 (B), R22.1 (R1.1), U2.45 (PMODE0)
unnamed: R22.4 (R4.1), U2.36 (INTN)
unnamed: C26.2, U2.22 (1V20)
unnamed: R20.2, U2.10 (EXRES1)
unnamed: R28.2, U2.37 (RSTN)
unnamed: C25.2, U2.20 (TOCAP)
unnamed: C29.1, R21.1, U2.30 (XI/CLKIN), Y2.1
unnamed: C30.1, R21.2, U2.31 (XO), Y2.3 (2)
unnamed: U3.1 (~MR), U3.8 (~WDO)
unnamed: R5.2, U3.7 (~RESET)
unnamed: C31.1, U8.5 (C1)
unnamed: C38.1, U9.21 (OSC1), Y3.3 (2)
unnamed: C37.1, U9.20 (OSC2), Y3.1
unnamed: R24.2, TP3.1, U9.2 (RESET)
unnamed: R25.2, TP4.1, U9.15 (STBY)
unnamed: R27.2, U10.3 (*SHDN)
unnamed: C42.2, U10.6 (C+)
unnamed: C42.1, U10.4 (C-)
RCT: C36.1, J5.6, R18.2, R19.2
RF1_ANT: C15.1, JP6.2 (B), L1.1, U4.1 (ANT), U5.9 (ANT)
RF1_IO0: IC1.35 (GPIO23), U4.6 (GPIO_0), U5.14 (DIO0)
RF1_IO4: IC1.34 (GPIO22), U4.4 (GPIO_4), U5.12 (BUSY)
RF1_RST: IC1.31 (GPIO20), U4.14 (RESET), U5.6 (~RESET)
RF_VCC: C14.2, JP7.2 (C), U4.5 (VCC), U5.13 (3V3)
RX: D2.2 (A), IC1.3 (GPIO1), J3.3
RX+: C18.2, R18.1, U2.6 (RXP)
RX-: C19.2, R19.1, U2.5 (RXN)
RXCAN: U9.5 (RXCAN), U9.10 (RXD)
SCL0: IC1.7 (GPIO5), J2.7, R6.1 (R1.1)
SCL1: IC1.5 (GPIO3), J3.4, J7.4, R6.3 (R3.1), U7.13 (SCL), U8.1 (SCL/SPC)
SDA0: IC1.6 (GPIO4), J2.8, R6.2 (R2.1)
SDA1: IC1.4 (GPIO2), J3.5, J7.3, R6.4 (R4.1), U7.14 (SDA), U8.4 (SDA/SDI/SDO)
SPI0_CS0: IC1.12 (GPIO9), J10.1, R13.2, U4.13 (NSS), U5.5 (CS)
SPI0_MISO: IC1.11 (GPIO8), J10.4, U4.10 (MISO), U5.2 (MISO)
SPI0_MOSI: IC1.14 (GPIO11), J10.3, U4.11 (MOSI), U5.3 (MOSI)
SPI0_SCK: IC1.13 (GPIO10), J10.2, U4.12 (SCK), U5.4 (SCK)
SPI1_CS0: IC1.28 (GPIO17), J4.2 (CD/DAT3), R15.1
SPI1_CS1: IC1.38 (GPIO26/AD0), U1.1 (*OE), U2.32 (SCSN)
SPI1_CS2: IC1.40 (GPIO28/AD2), R23.2, U9.1 (CS)
SPI1_MISO: IC1.27 (GPIO16), J4.7 (DAT0), U1.4 (Y), U9.28 (SO)
SPI1_MOSI: IC1.30 (GPIO19), J4.3 (CMD), U2.35 (MOSI), U9.27 (SI)
SPI1_SCK: IC1.29 (GPIO18), J4.5 (CLK), U2.33 (SCLK), U9.26 (SCK)
SWCLK: IC1.24 (SWCLK), J1.4 (SWDCLK/TCK)
SWDIO: IC1.25 (SWDIO), J1.2 (SWDIO/TMS)
TCT: C17.1, J5.3, R17.2
TX: D1.2 (A), IC1.2 (GPIO0), J3.2
TX+: J5.1, R14.2, U2.2 (TXP)
TX-: J5.2, R16.2, U2.1 (TXN)
TXCAN: U9.4 (TXCAN), U9.16 (TXD)
USB_D+: J8.3 (D+), J9.3, R7.2
USB_D-: J8.2 (D-), J9.2, R8.2
VBUS: C12.1, D7.2 (A), IC2.3 (INPUT), J8.1 (VBUS), J9.1, R9.1
VBUS_RESET: IC1.17 (GPIO14), J2.3
VCC_RF1: J2.11, J11.3, J12.3, JP2.1 (A), JP7.1 (A)
VDDA: C20.1, C21.1, C22.1, C23.1, C24.1, FB1.2, R14.1, R16.1, R17.1, U2.4 (AVDD), U2.8 (AVDD), U2.11 (AVDD), U2.15 (AVDD), U2.17 (AVDD), U2.21 (AVDD)
WDT_WDI: IC1.32 (GPIO21), U3.6 (~WDI)
YELLOWLED: J5.9, U2.27 (ACTLED)
firm_active: IC1.39 (GPIO27/AD1), R11.1

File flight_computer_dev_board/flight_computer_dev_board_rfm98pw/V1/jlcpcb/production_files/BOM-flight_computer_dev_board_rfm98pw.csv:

Comment,Designator,Footprint,LCSC
FerriteBead,"FB1,FB2",R_0603_1608Metric,C1002
10k,"R22,R6",R_Array_Convex_4x0603,C111802
1k,R2,R_0402_1005Metric,C11702
LED,"D1,D3",LED_0603_1608Metric,C12065
LSM303AGRTR,U8,LGA-12_2x2mm_P0.5mm,C126671
0.1uF,"C20,C21,C22,C23,C26,C28",C_0603_1608Metric,C14663
10nf,"C17,C36",C_0402_1005Metric,C15195
100nf,"C10,C11,C32,C33,C34,C35,C4,C5,C7,C9",C_0402_1005Metric,C1525
6.8nf,"C18,C19",C_0402_1005Metric,C1542
22pF,"C1,C2,C29,C30,C37,C38",C_0402_1005Metric,C1555
47pf,"C39,C40",C_0402_1005Metric,C1567
PESD1CAN,D8,SOT-23-3,C15771
1uF,"C3,C42,C6,C8",C_0603_1608Metric,C15849
10uF,"C24,C25,C27",C_0805_2012Metric,C15850
BM04B-SRSS-TB(LF)(SN),"J10,J11,J12,J9",JST_BM04B-SRSS-TB(LF)(SN),C160390
Breakout,"J13,J7",JST_SH_SM04B-SRSS-TB_1x04-1MP_P1.00mm_Horizontal,C160404
220nf,C31,C_0402_1005Metric,C16772
10uF,"C12,C14,C41,C43",C_0603_1608Metric,C19702
RP2040_QFN56,IC1,QFN-56-1EP_7x7mm_P0.4mm_EP3.2x3.2mm_ThermalVias,C2040
1k,"R10,R3,R4",R_0603_1608Metric,C21190
120,R26,R_0603_1608Metric,C22787
10,R17,R_0603_1608Metric,C22859
LED,D2,LED_0603_1608Metric,C2286
12.4k,R20,R_0603_1608Metric,C22865
1M,R21,R_0603_1608Metric,C22935
49.9,"R14,R16,R18,R19",R_0603_1608Metric,C23185
22,"R7,R8",R_0603_1608Metric,C23345
USB_B_Micro,J8,MOLEX_105164-0001,C234179
12MHZ,Y1,Crystal_SMD_2520-4Pin_2.5x2.0mm,C252259
10k,R15,R_0402_1005Metric,C25744
10k,"R1,R11,R12,R13,R23,R24,R25,R27,R28,R5,R9",R_0603_1608Metric,C25804
LSM6DSOTR,U7,LGA-14_3x2.5mm_P0.5mm_LayoutBorder3x4y,C2655100
MAX706RESA,U3,SO-8_3.9x4.9mm_P1.27mm,C28380
16MHZ 12 pf,Y3,Crystal_SMD_2520-4Pin_2.5x2.0mm,C284158
WS2812B_SK6812_1515,LED1,LED_WS2812B_PLCC4_5.0x5.0mm_P3.2mm,C2843785
25MHz,Y2,Crystal_SMD_3225-4Pin_3.2x2.5mm,C2933043
W5500,U2,LQFP-48_7x7mm_P0.5mm,C32843
AP3602AKTR-G1,U10,SOT-23-6,C460358
NSR0320,"D4,D7",D_SOD-323F,C48192
104031-0811,J4,microSD_HC_Molex_104031-0811,C585350
22uF,C13,C_0603_1608Metric,C59461
KMR2,"SW1,SW2",BTN_KMR2_4.6X2.8,C72443
SN74AHC1G125DBVR,U1,SOT-23-5,C7468
RJ45_LED_Shielded,J5,RB1-125BAG1A_WIZ,C910370
AZ1117CH-3.3TRG1,IC2,SOT-223,C92102
W25Q128JV,U6,SOIC-8_5.275x5.275mm_P1.27mm,C97521
LED,D5,LED_0603_1608Metric,C99290
Conn_Coaxial,J6,SMA_Amphenol_901-144_Vertical,
DNI,C16,C_0603_1608Metric,
DNI,L1,R_0603_1608Metric,
SolderJumper_2_Open,JP1,SolderJumper-2_P1.3mm_Open_RoundedPad1.0x1.5mm,
DNI,C15,C_0603_1608Metric,
RFM98PW,U4,RFM98PW,
RESET,TP2,TestPoint_Loop_D1.80mm_Drill1.0mm_Beaded,
SolderJumper_2_Open,JP6,SolderJumper-2_P1.3mm_Open_RoundedPad1.0x1.5mm,
SolderJumper_2_Open,JP5,SolderJumper-2_P1.3mm_Open_RoundedPad1.0x1.5mm,
RFM9xBreakout,U5,HOPERF_RFM9XW_SMD,
SolderJumper_2_Open,JP2,SolderJumper-2_P1.3mm_Open_RoundedPad1.0x1.5mm,
SolderJumper_2_Open,JP4,SolderJumper-2_P1.3mm_Open_RoundedPad1.0x1.5mm,
FC to EPS Connector,J2,Molex_Pico-Lock_504050-1291_1x12-1MP_P1.50mm_Horizontal,
USBBOOT,TP1,TestPoint_Loop_D1.80mm_Drill1.0mm_Beaded,
SolderJumper_2_Open,JP3,SolderJumper-2_P1.3mm_Open_RoundedPad1.0x1.5mm,
Life Makes Lemonade,J3,PinHeader_1x06_P2.54mm_Vertical,
Conn_ARM_JTAG_SWD_10,J1,JTAG_2X05_1.27MM_BOX_NOCREAM,
SolderJumper_2_Open,JP8,SolderJumper-2_P1.3mm_Open_RoundedPad1.0x1.5mm,
MCP25625-E/ML,U9,QFN-28-1EP_6x6mm_P0.65mm_EP4.25x4.25mm,
Standby,TP4,TestPoint_Loop_D1.80mm_Drill1.0mm_Beaded,
RESET,TP3,TestPoint_Loop_D1.80mm_Drill1.0mm_Beaded,
SolderJumper_3_Open,JP7,SolderJumper-3_P1.3mm_Open_RoundedPad1.0x1.5mm_NumberLabels,
